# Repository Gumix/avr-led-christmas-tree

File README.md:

View this project on [CADLAB.io](https://cadlab.io/node/796). 

# avr-led-christmas-tree

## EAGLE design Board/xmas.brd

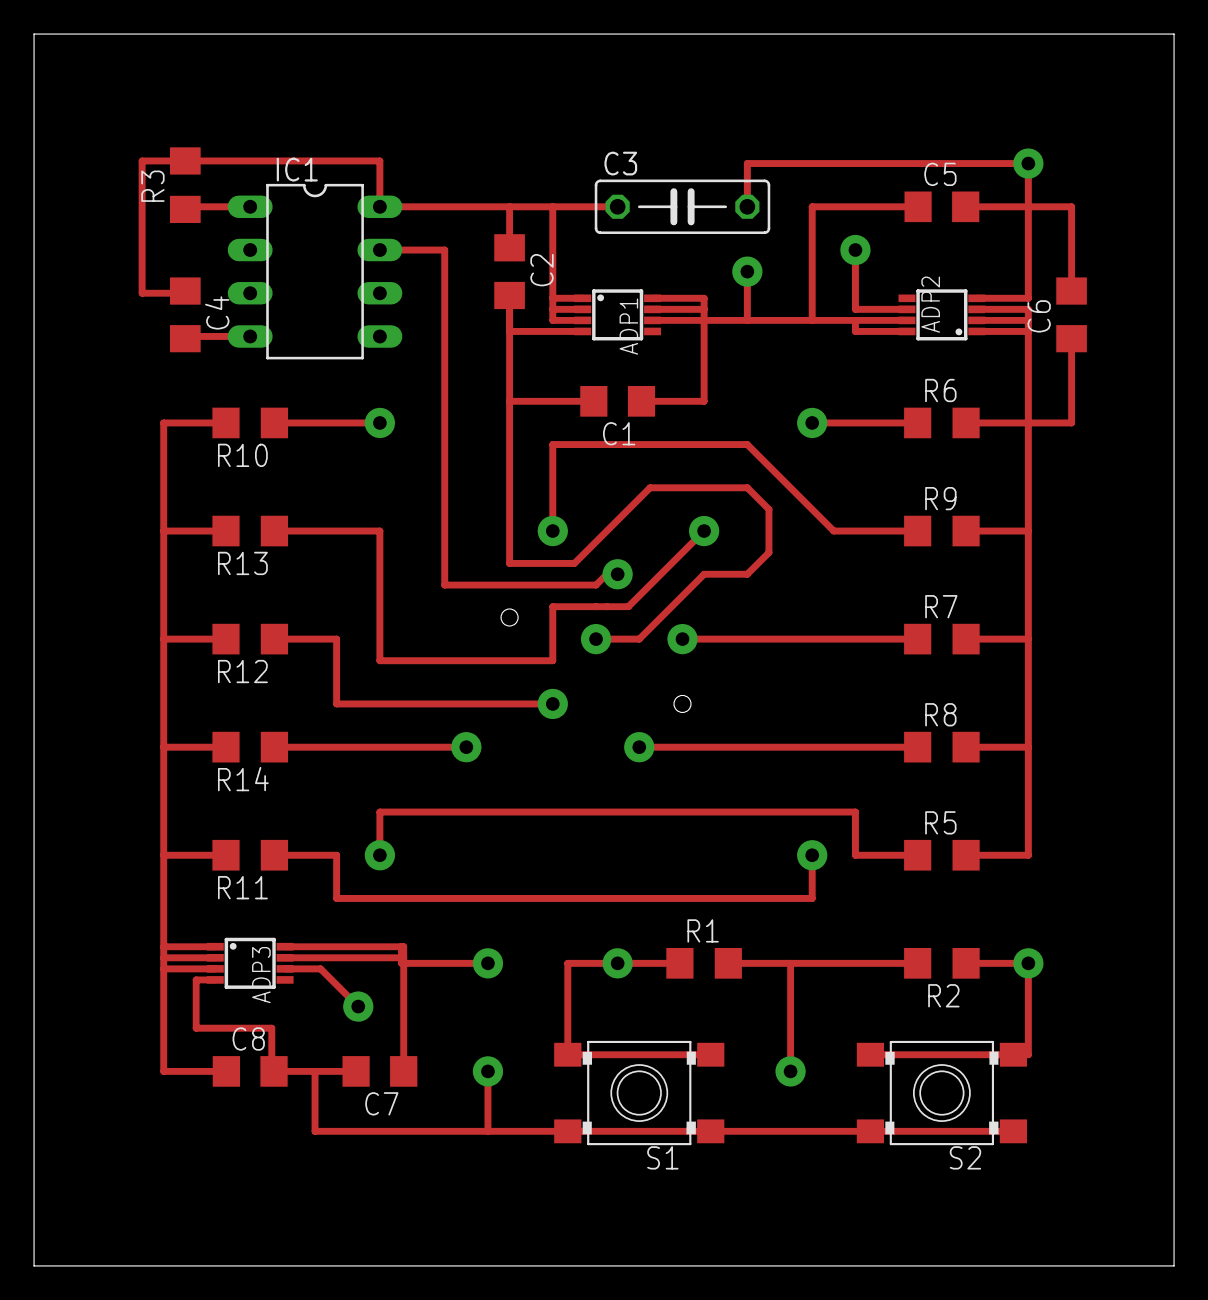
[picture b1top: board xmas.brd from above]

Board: 2 copper layers, 67.0 x 72.4 mm, 48 parts (0 on the bottom side), 21 nets.

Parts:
ADP1, ADP2, ADP3: ADP3335MSOP8; MSOP8
C1, C2, C4, C5, C6, C7, C8: 1uF; C1206
C3: 47uF; C075-032X103
IC1: TINY13-20PU; DIL08
LSP1, LSP2, LSP3, LSP4, LSP5, LSP6, LSP7, LSP8, LSP9, LSP10, LSP11, LSP12, LSP13, LSP14, LSP15, LSP16, LSP17, LSP18, LSP19, LSP20, LSP21: LSP10
R1, R2, R3: 10k; R1206
R5, R6, R7, R8, R9, R10, R11, R12, R13, R14: 30; R1206
S1, S2: SKHMPSE010; SKHMPXE010

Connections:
+5V: ADP1.OUT1, ADP1.OUT2, ADP1.OUT3, C2.1, C3.1, C4.1, IC1.8, LSP20.MP, R1.2, R2.2, R3.2
GND: ADP1.GND, ADP2.GND, ADP3.GND, C1.2, C2.2, C3.2, C4.2, C5.2, C6.2, C7.2, C8.2, IC1.4, LSP13.MP, LSP14.MP, LSP16.MP, S1.1, S1.2, S2.1, S2.2
unnamed: IC1.2, LSP17.MP, R1.1, S1.3, S1.4
unnamed: IC1.3, LSP19.MP, R2.1, S2.3, S2.4
unnamed: IC1.1, R3.1
unnamed: ADP2.OUT1, ADP2.OUT2, ADP2.OUT3, C6.1, R5.2, R6.2, R7.2, R8.2, R9.2
unnamed: LSP1.MP, R5.1
unnamed: IC1.7, LSP11.MP
unnamed: LSP2.MP, R6.1
unnamed: LSP3.MP, R7.1
unnamed: LSP4.MP, R8.1
unnamed: LSP5.MP, R9.1
unnamed: LSP6.MP, R10.1
unnamed: ADP3.OUT1, ADP3.OUT2, ADP3.OUT3, C8.1, R10.2, R11.2, R12.2, R13.2, R14.2
unnamed: LSP7.MP, R11.1
unnamed: LSP8.MP, R12.1
unnamed: LSP9.MP, R13.1
unnamed: LSP10.MP, R14.1
OC0A: ADP2.SD, IC1.5, LSP18.MP
OC0B: ADP3.SD, IC1.6, LSP15.MP
VCC: ADP1.IN1, ADP1.IN2, ADP1.SD, ADP2.IN1, ADP2.IN2, ADP3.IN1, ADP3.IN2, C1.1, C5.1, C7.1, LSP12.MP, LSP21.MP

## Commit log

2017-06-04 Add sch, brd and skp
2017-10-12 Add aps
2018-03-27 Backlink to CADLAB.io has been added.
